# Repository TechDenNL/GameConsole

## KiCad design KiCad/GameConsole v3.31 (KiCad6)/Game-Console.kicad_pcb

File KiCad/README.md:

KiCad6 Archive Project file. 
Use; KiCad6 -> file -> Unarchive Project to open project on your own computer

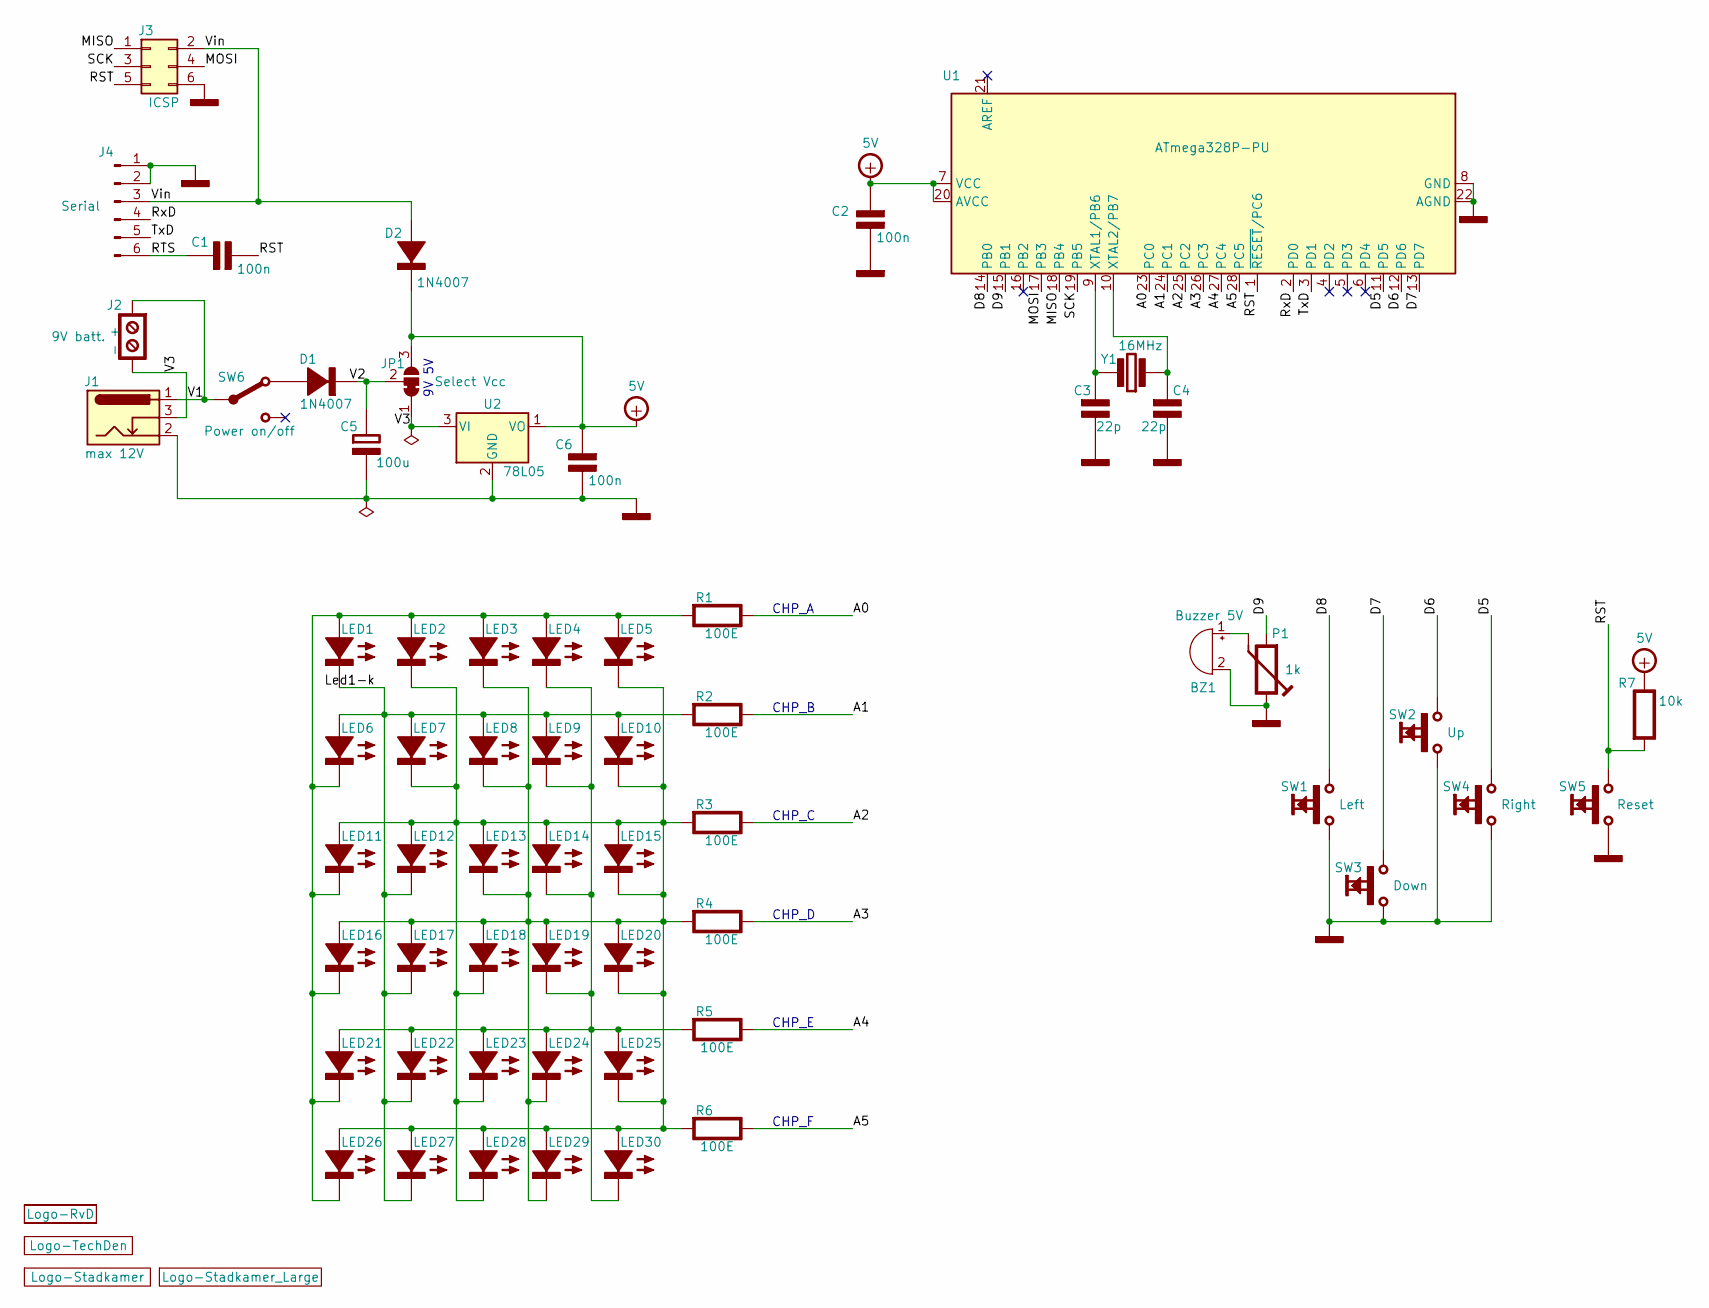
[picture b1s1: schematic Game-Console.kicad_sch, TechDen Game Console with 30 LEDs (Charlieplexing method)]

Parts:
BZ1: Buzzer 5V; MagneticBuzzer_ProSignal_ABT-410-RC
C1, C2, C6: 100n; C_Rect_L7.0mm_W3.5mm_P2.50mm_P5.00mm; Rating V
C3, C4: 22p; C_Rect_L7.0mm_W3.5mm_P2.50mm_P5.00mm; Rating V
C5: 100u; CP_Radial_D6.3mm_P2.50mm
D1, D2: 1N4007; D_DO-41_SOD81_P10.16mm_Horizontal
J1: Barrel_Jack_Switch; BarrelJack_Horizontal
J2: 9V batt.; TerminalBlock_Phoenix_MKDS-1,5-2-5.08_1x02_P5.00&P5.08mm_Ho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
J3: ICSP; PinHeader_2x03_P2.54mm_Vertical
J4: Serial; PinSocket_1x06_P2.54mm_Horizontal
JP1: Select Vcc; SolderJumper-3_P1.3mm_Bridged2Bar12_Pad1.0x1.5mm_NumberLabe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
L1: Logo-RvD; RvD Logo inverted small
L2: Logo-TechDen; TechDen Logo - inverted
L3: Logo-Stadkamer; Stadkamer Logo
L4: Logo-Stadkamer_Large; Stadkamer Logo_large
LED1, LED2, LED3, LED4, LED5, LED6, LED7, LED8, LED9, LED10, LED11, LED12, LED13, LED14, LED15, LED16, LED17, LED18, LED19, LED20, LED21, LED22, LED23, LED24, LED25, LED26, LED27, LED28, LED29, LED30: LED; LED_D3.0mm
P1: 1k; Potentiometer_Bourns_3386X_Horizontal
R1, R2, R3, R4, R5, R6: 100E; R_Axial_DIN0207_L6.3mm_D2.5mm_P10.16mm_Horizontal
R7: 10k; R_Axial_DIN0207_L6.3mm_D2.5mm_P10.16mm_Horizontal
SW1: Left; SW_PUSH_6mm
SW2: Up; SW_PUSH_6mm
SW3: Down; SW_PUSH_6mm
SW4: Right; SW_PUSH_6mm
SW5: Reset; SW_PUSH_6mm
SW6: Power on/off; switch_MSK-12D19; Rating V/A
U1: ATmega328P-PU; DIP-28_W7.62mm
U2: 78L05; TO-92_Wide
Y1: 16MHz; Crystal_HC49-4H_Vertical

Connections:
/A0: R1.1 (+), U1.23 (PC0)
/A1: R2.1 (+), U1.24 (PC1)
/A2: R3.1 (+), U1.25 (PC2)
/A3: R4.1 (+), U1.26 (PC3)
/A4: R5.1 (+), U1.27 (PC4)
/A5: R6.1 (+), U1.28 (PC5)
/D5: SW4.1, U1.11 (PD5)
/D6: SW2.1, U1.12 (PD6)
/D7: SW3.1, U1.13 (PD7)
/D8: SW1.1, U1.14 (PB0)
/D9: P1.1 (a), U1.15 (PB1)
/Led1-k: LED1.1 (K-), LED6.2 (A+), LED7.2 (A+), LED8.2 (A+), LED9.2 (A+), LED10.2 (A+), LED12.1 (K-), LED17.1 (K-), LED22.1 (K-), LED27.1 (K-), R2.2 (-)
/MISO: J3.1, U1.18 (PB4)
/MOSI: J3.4, U1.17 (PB3)
/RST: C1.2 (-), J3.5, R7.2 (-), SW5.2, U1.1 (~RESET/PC6)
/RTS: C1.1 (+), J4.6
/RxD: J4.4, U1.2 (PD0)
/SCK: J3.3, U1.19 (PB5)
/TxD: J4.5, U1.3 (PD1)
/V1: J1.1, J2.1, SW6.1
/V2: C5.1 (+), D1.1 (K-), JP1.2 (C)
/V3: J1.3, J2.2, JP1.1 (A), U2.3 (VI)
/Vin: D2.2 (A+), J3.2, J4.3
GND: BZ1.2 (+), C2.2 (-), C3.2 (-), C4.2 (-), C5.2 (-), C6.2 (-), J1.2, J3.6, J4.1, J4.2, P1.3 (c), SW1.2, SW2.2, SW3.2, SW4.2, SW5.1, U1.8 (GND), U1.22 (AGND), U2.2 (GND)
unnamed: BZ1.1 (-), P1.2 (b)
unnamed: C3.1 (+), U1.9 (XTAL1/PB6), Y1.1 (+)
unnamed: C4.1 (+), U1.10 (XTAL2/PB7), Y1.2 (-)
unnamed: D1.2 (A+), SW6.2
unnamed: LED1.2 (A+), LED2.2 (A+), LED3.2 (A+), LED4.2 (A+), LED5.2 (A+), LED6.1 (K-), LED11.1 (K-), LED16.1 (K-), LED21.1 (K-), LED26.1 (K-), R1.2 (-)
unnamed: LED2.1 (K-), LED3.1 (K-), LED5.1 (K-), LED7.1 (K-), LED8.1 (K-), LED10.1 (K-), LED11.2 (A+), LED12.2 (A+), LED13.1 (K-), LED13.2 (A+), LED14.2 (A+), LED15.1 (K-), LED15.2 (A+), LED16.2 (A+), LED17.2 (A+), LED18.1 (K-), LED18.2 (A+), LED19.2 (A+), LED20.1 (K-), LED20.2 (A+), LED23.1 (K-), LED24.1 (K-), LED25.1 (K-), LED26.2 (A+), LED27.2 (A+), LED28.1 (K-), LED28.2 (A+), LED29.1 (K-), LED29.2 (A+), LED30.2 (A+), R3.2 (-), R4.2 (-), R6.2 (-)
unnamed: LED4.1 (K-), LED9.1 (K-), LED14.1 (K-), LED19.1 (K-), LED21.2 (A+), LED22.2 (A+), LED23.2 (A+), LED24.2 (A+), LED25.2 (A+), LED30.1 (K-), R5.2 (-)
V+: C2.1 (+), C6.1 (+), D2.1 (K-), JP1.3 (B), R7.1 (+), U1.7 (VCC), U1.20 (AVCC), U2.1 (VO)

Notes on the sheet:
CHP_E
CHP_A
CHP_D
CHP_B
CHP_C
CHP_F

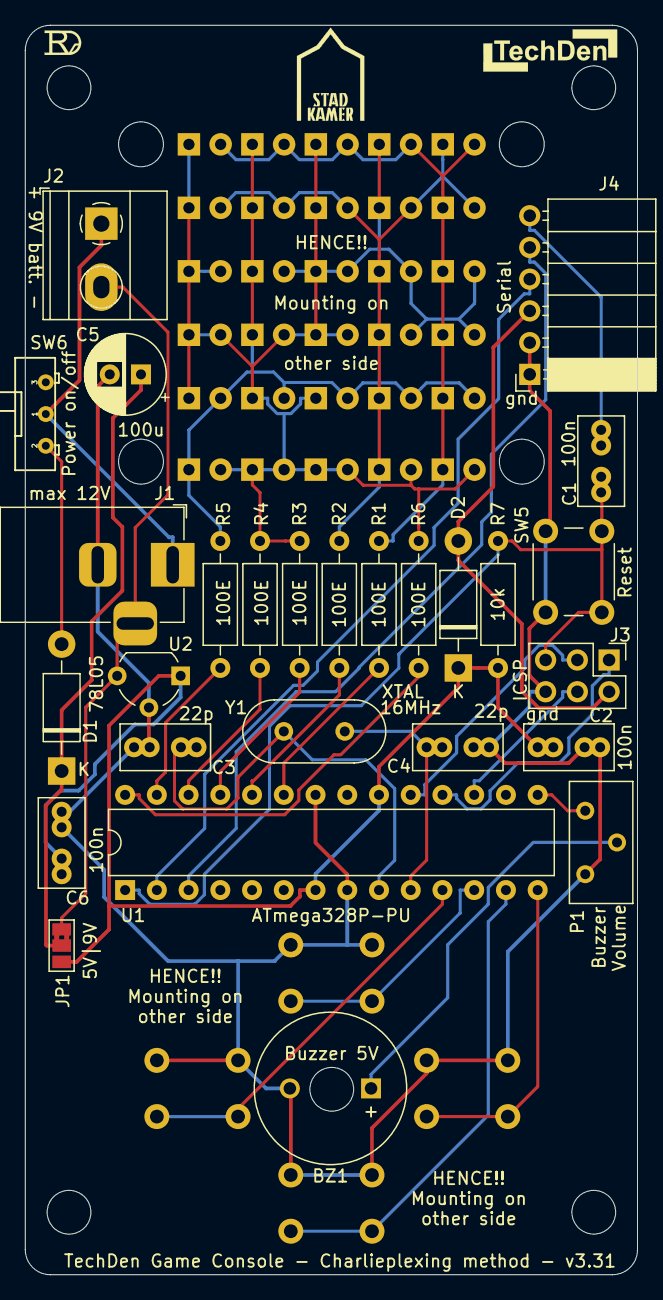
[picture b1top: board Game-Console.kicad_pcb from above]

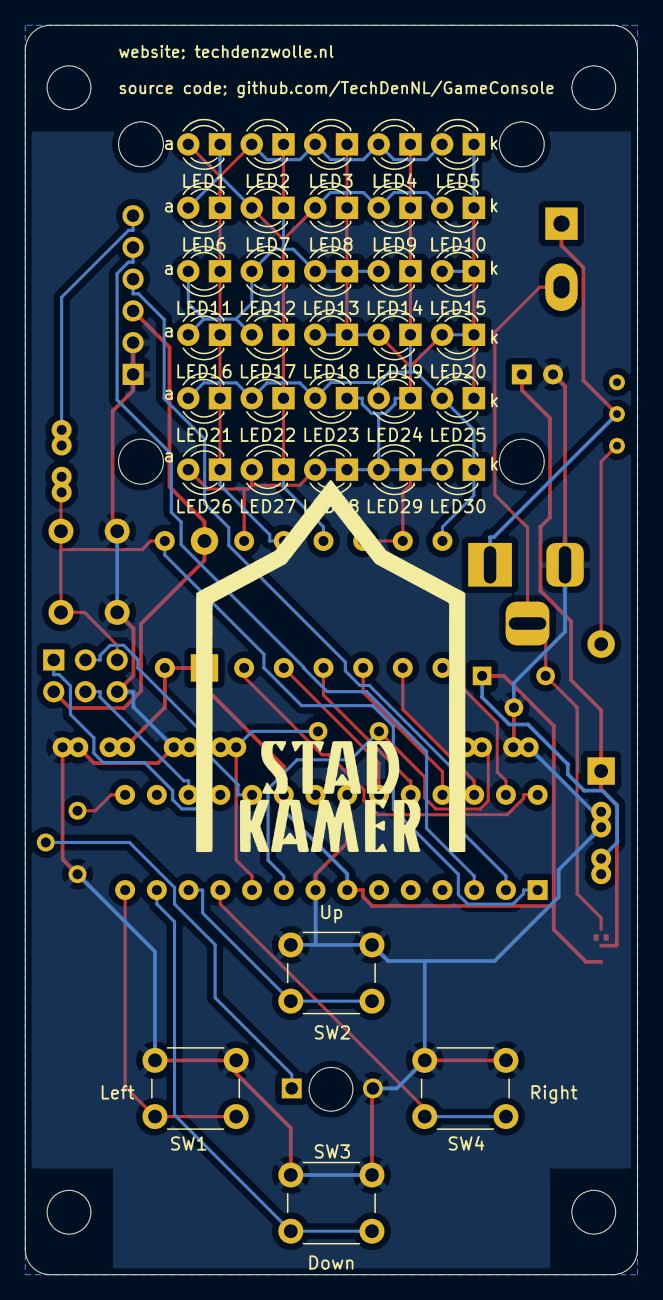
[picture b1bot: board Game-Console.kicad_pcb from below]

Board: 2 copper layers, 49.0 x 100.0 mm, 65 parts (35 on the bottom side), 32 nets.

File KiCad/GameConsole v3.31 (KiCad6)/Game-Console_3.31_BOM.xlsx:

Component | References | Value | Quantity Per PCB
1 | BZ1 | Buzzer 5V | 1
2 | C3-C4 | 22p | 2
3 | C1-C2 C6 | 100n | 3
4 | C5 | 100u | 1
5 | D1-D2 | 1N4007 | 2
6 | J2 | 9V batt. | 1
7 | J1 | Barrel_Jack_Switch | 1
8 | J3 | ICSP | 1
9 | J4 | Serial | 1
10 | LED1-LED30 | LED | 30
11 | P1 | 1k | 1
12 | R7 | 10k | 1
13 | R1-R6 | 100E | 6
14 | SW3 | Down | 1
15 | SW1 | Left | 1
16 | SW6 | Power on/off | 1
17 | SW5 | Reset | 1
18 | SW4 | Right | 1
19 | SW2 | Up | 1
20 | U2 | 78L05 | 1
21 | U1 | ATmega328P-PU | 1
22 | Y1 | 16MHz | 1
Component Groups: | 22
Component Count: | 60
Fitted Components: | 60
Number of PCBs: | 1
Total components: | 60
Schematic Version: | 3.31
Schematic Date: | 2022-04-25
BoM Date: | 26/04/2022 21:08:47
Schematic Source: | Game-Console.kicad_sch
KiCad Version: | Eeschema (6.0.4)

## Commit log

2021-09-06 Initial files Roland
2021-09-13 Refactor
    Removed obsolete files.
    Moved documentation files
2021-11-08 Created race game for console(wip)
2022-07-11 wip run
2022-07-28 GameConsole v3.31
    KiCad files version 3.31 added
    Docs updates
    Presentations added
2022-08-08 Update
    Update of my games
    Update prestation september
    KiCad6 ProjectArchive
2022-08-22 Create TechDen presentatie v03.pptx
    Update presentatie
2022-08-22 Update presentatie
2022-09-07 Added wip presentation
2023-01-31 Update after workshop experience
2023-02-21 update montage instructie
    update montage instructie
2023-02-22 Update montage instructie
2023-02-23 Workshop Elektronica
2023-03-03 Workshop E-Comp added
